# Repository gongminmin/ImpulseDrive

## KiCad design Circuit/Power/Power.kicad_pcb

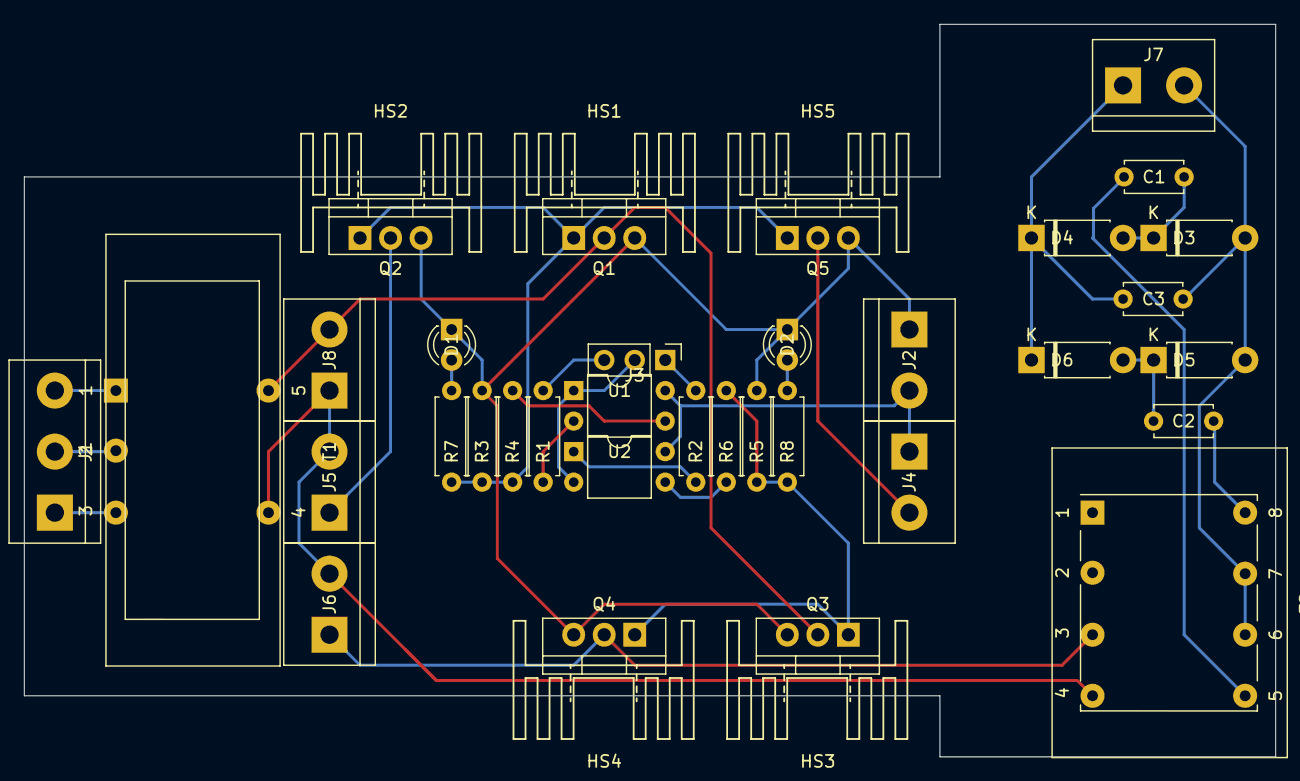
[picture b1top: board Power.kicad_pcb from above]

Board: 2 copper layers, 104.1 x 61.0 mm, 39 parts (0 on the bottom side), 27 nets.

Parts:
C1, C2, C3: 1nF; C_Disc_D4.7mm_W2.5mm_P5.00mm
D1: Discharge; LED_D3.0mm_FlatTop
D2: Charge; LED_D3.0mm_FlatTop
D3, D4, D5, D6: 1N4007; D_DO-41_SOD81_P7.62mm_Horizontal
HS1, HS2, HS3, HS4, HS5: Heatsink; Heatsink_TO220_15x10mm
J1: 12V AC In; TerminalBlock_bornier-3_P5.08mm
J2: DC In; TerminalBlock_bornier-2_P5.08mm
J3: From Control; PinHeader_1x03_P2.54mm_Vertical
J4: To Coil; TerminalBlock_bornier-2_P5.08mm
J5: To Starter; TerminalBlock_bornier-2_P5.08mm
J6: To Capacitor; TerminalBlock_bornier-2_P5.08mm
J7: To Capacitors; TerminalBlock_bornier-2_P5.08mm
J8: AC In; TerminalBlock_bornier-2_P5.08mm
Q1, Q2, Q3, Q4, Q5: RFP30N06LE; TO-220-3_Vertical
R1, R2: 1K; R_Axial_DIN0207_L6.3mm_D2.5mm_P7.62mm_Horizontal
R3, R4, R5, R6: 10K; R_Axial_DIN0207_L6.3mm_D2.5mm_P7.62mm_Horizontal
R7, R8: 3K3; R_Axial_DIN0207_L6.3mm_D2.5mm_P7.62mm_Horizontal
T1: 7+7:14; Transformer_Toroid_5Pin
T2: 6:200; Transformer_Generic_EE25_8Pin
U1, U2: PC817; DIP-4_W7.62mm

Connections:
+12V: J2.2, J4.1, U1.4, U2.4
/AC0In: J1.2, T1.2
/AC+In: J1.3, T1.1
/AC-In: J1.1, T1.3
/CapacitorPower+: C3.1, D4.1, D6.1, J7.1
/CapacitorPower-: C3.2, D3.2, D5.2, J7.2, T2.6, T2.7
/Coil-: J4.2, Q5.2
/ControlGND: J3.3, R1.1
/ControlPower: J3.1, R2.1
/ControlSignal: J3.2, U1.1, U2.2
/StarterPower+: J5.1, Q2.2
/StarterPower-: J5.2, J6.2, J8.1, T1.4, T2.4
GND: D1.1, D2.1, J2.1, Q1.3, Q2.3, Q3.3, Q4.3, Q5.3, R3.1, R5.2
unnamed: C1.1, D3.1, D4.2
unnamed: C1.2, T2.5
unnamed: C2.1, D5.1, D6.2
unnamed: C2.2, T2.8
unnamed: D1.2, R7.1
unnamed: D2.2, R8.2
unnamed: J6.1, Q4.2, T2.3
unnamed: J8.2, Q1.2, Q3.2, T1.5
unnamed: Q1.1, Q2.1, Q5.1, R3.2, R4.2, R7.2
unnamed: Q3.1, Q4.1, R5.1, R6.2, R8.1
unnamed: R1.2, U1.2
unnamed: R2.2, U2.1
unnamed: R4.1, U1.3
unnamed: R6.1, U2.3

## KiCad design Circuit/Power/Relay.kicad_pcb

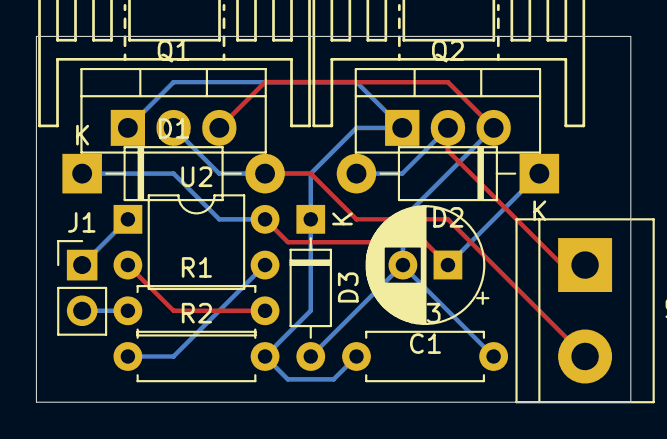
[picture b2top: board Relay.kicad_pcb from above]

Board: 2 copper layers, 33.0 x 20.3 mm, 14 parts (0 on the bottom side), 9 nets.

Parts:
C1: 100uF; CP_Radial_D6.3mm_P2.50mm
D1, D2: 1N4007; D_DO-41_SOD81_P10.16mm_Horizontal
D3: 1N5242B; D_DO-35_SOD27_P7.62mm_Horizontal
HS1, HS2: Heatsink; Heatsink_TO220_15x10mm
J1: Input; PinHeader_1x02_P2.54mm_Vertical
J2: Output; TerminalBlock_bornier-2_P5.08mm
Q1, Q2: RFP30N06LE; TO-220-3_Vertical
R1: 1K; R_Axial_DIN0207_L6.3mm_D2.5mm_P7.62mm_Horizontal
R2, R3: 10K; R_Axial_DIN0207_L6.3mm_D2.5mm_P7.62mm_Horizontal
U2: PC817; DIP-4_W7.62mm

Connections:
/Input+: J1.1, U2.1
/Input-: J1.2, R1.1
/Output1: D1.2, J2.2, Q1.2
/Output2: D2.2, J2.1, Q2.2
unnamed: C1.1, D1.1, D2.1, U2.4
unnamed: C1.2, D3.2, Q1.3, Q2.3, R3.2
unnamed: D3.1, Q1.1, Q2.1, R2.2, R3.1
unnamed: R1.2, U2.2
unnamed: R2.1, U2.3

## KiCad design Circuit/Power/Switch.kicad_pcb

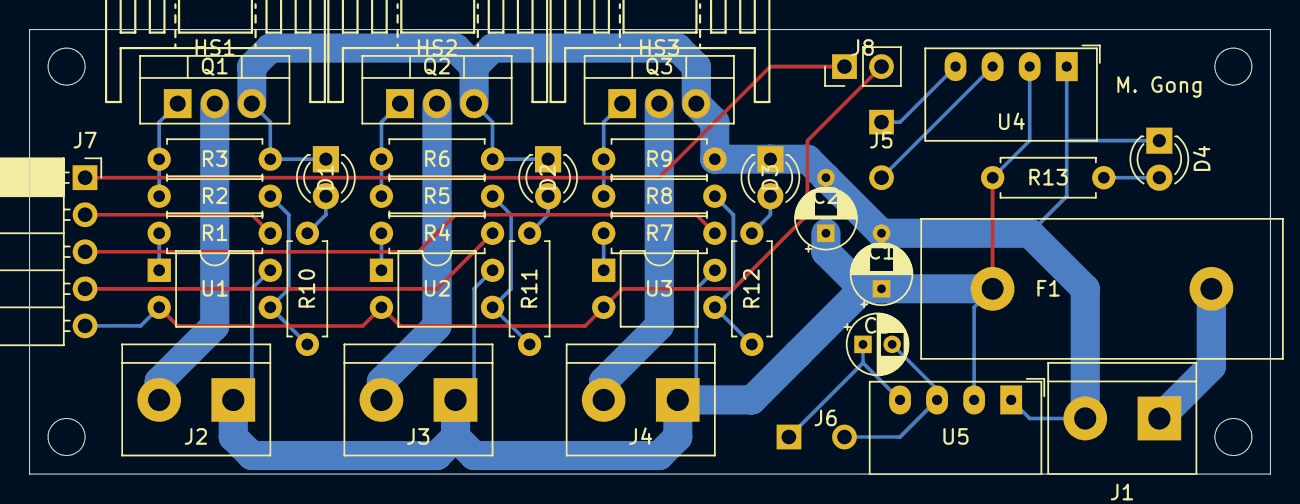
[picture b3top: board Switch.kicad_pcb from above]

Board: 2 copper layers, 85.1 x 30.5 mm, 40 parts (0 on the bottom side), 28 nets.

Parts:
C1, C3: 10uF; CP_Radial_D4.0mm_P2.00mm
C2: 2.2uF; CP_Radial_D4.0mm_P2.00mm
D1, D2, D3, D4: LED; LED_D3.0mm_FlatTop
F1: Fuse; Fuseholder_Cylinder-5x20mm_ASI_PTF-76-10_Horizontal_Open
HS1, HS2, HS3: Heatsink; Heatsink_TO220_15x10mm
J1: Main Power In; TerminalBlock_bornier-2_P5.08mm
J2: To Starter; TerminalBlock_bornier-2_P5.08mm
J3: To Capacitor; TerminalBlock_bornier-2_P5.08mm
J4: To Injector; TerminalBlock_bornier-2_P5.08mm
J5: To Coil; SolderWirePad_1x02_P3.81mm_Drill1mm
J6: To Control Power; SolderWirePad_1x02_P3.81mm_Drill1mm
J7: From Control; PinSocket_1x05_P2.54mm_Horizontal
J8: To Coil Signal; PinHeader_1x02_P2.54mm_Vertical
Q1, Q2, Q3: RFP30N06LE; TO-220-3_Vertical
R1, R4, R7: 680; R_Axial_DIN0207_L6.3mm_D2.5mm_P7.62mm_Horizontal
R2, R5, R8: 4.7K; R_Axial_DIN0207_L6.3mm_D2.5mm_P7.62mm_Horizontal
R3, R6, R9: 10K; R_Axial_DIN0207_L6.3mm_D2.5mm_P7.62mm_Horizontal
R10, R11, R12, R13: 2.2K; R_Axial_DIN0207_L6.3mm_D2.5mm_P7.62mm_Horizontal
U1, U2, U3: PC817; DIP-4_W7.62mm
U4: B1212S; Converter_DCDC_muRata_CRE1xxxxxxSC_THT
U5: B1205S; Converter_DCDC_muRata_CRE1xxxxxxSC_THT

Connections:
/CapacitorPower+: C1.1, C2.1, F1.1, J2.1, J3.1, J4.1, R13.1, U1.4, U2.4, U3.4, U4.2, U5.2
/CapacitorPower-: J3.2, Q2.2
/CapacitorSignal: J7.4, R4.1
/CoilPower+: J5.1, U4.4
/CoilPower-: J5.2, U4.3
/CoilSignal: J7.1, J8.1
/ControlPower+: C3.1, J6.1, U5.4
/ControlPower-: C3.2, J6.2, U5.3
/InjectorPower-: J4.2, Q3.2
/InjectorSignal: J7.3, R7.1
/PowerIn+: F1.2, J1.1
/PowerIn-: C1.2, C2.2, D1.1, D2.1, D3.1, D4.1, J1.2, Q1.3, Q2.3, Q3.3, R3.2, R6.2, R9.2, U4.1, U5.1
/SignalGND: J7.5, J8.2, U1.2, U2.2, U3.2
/StarterPower-: J2.2, Q1.2
/StarterSignal: J7.2, R1.1
unnamed: D1.2, R10.2
unnamed: D2.2, R11.2
unnamed: D3.2, R12.2
unnamed: D4.2, R13.2
unnamed: Q1.1, R2.2, R3.1
unnamed: Q2.1, R5.2, R6.1
unnamed: Q3.1, R8.2, R9.1
unnamed: R1.2, U1.1
unnamed: R4.2, U2.1
unnamed: R7.2, U3.1
unnamed: R2.1, R10.1, U1.3
unnamed: R5.1, R11.1, U2.3
unnamed: R8.1, R12.1, U3.3

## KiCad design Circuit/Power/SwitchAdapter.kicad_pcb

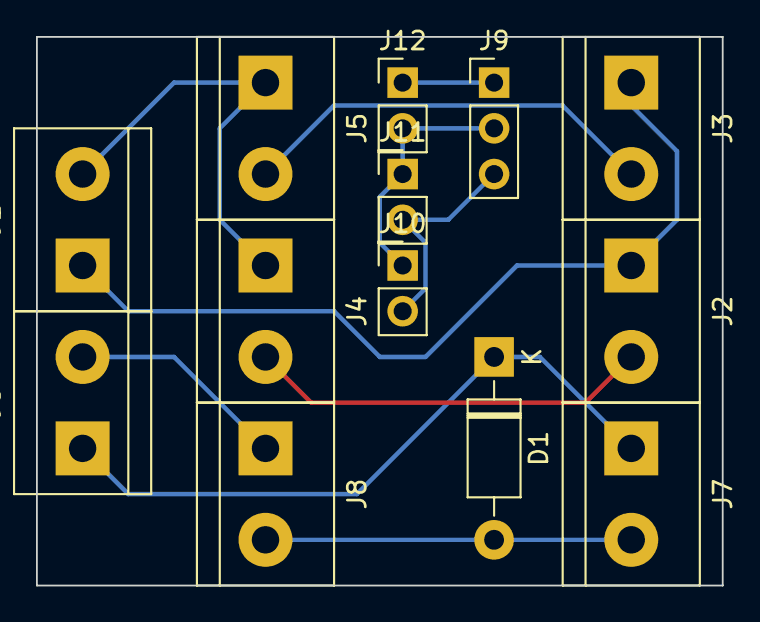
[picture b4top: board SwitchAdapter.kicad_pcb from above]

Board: 2 copper layers, 38.1 x 30.5 mm, 13 parts (0 on the bottom side), 10 nets.

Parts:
D1: 1N4007; D_DO-41_SOD81_P10.16mm_Horizontal
J1: Power AC In; TerminalBlock_bornier-2_P5.08mm
J2: To Starter; TerminalBlock_bornier-2_P5.08mm
J3: To Capacitor; TerminalBlock_bornier-2_P5.08mm
J4: Starter Relay Output; TerminalBlock_bornier-2_P5.08mm
J5: Capacitor Relay Output; TerminalBlock_bornier-2_P5.08mm
J6: DC In; TerminalBlock_bornier-2_P5.08mm
J7: To Coil; TerminalBlock_bornier-2_P5.08mm
J8: Coil Relay Output; TerminalBlock_bornier-2_P5.08mm
J9: From Control; PinHeader_1x03_P2.54mm_Vertical
J10: Coil Signal; PinHeader_1x02_P2.54mm_Vertical
J11: Starter Signal; PinHeader_1x02_P2.54mm_Vertical
J12: Capacitor Signal; PinHeader_1x02_P2.54mm_Vertical

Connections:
/CapacitorPower+: J3.2, J5.2
/CapacitorPower-: J1.1, J2.1, J3.1
/CapacitorRelayIn: J1.2, J4.1, J5.1
/CapacitorSignal+: J9.1, J12.1
/CapacitorSignal-: J9.2, J10.1, J11.1, J12.2
/CoilPower+: D1.1, J6.1, J7.1
/CoilPower-: J6.2, J8.1
/CoilRelayOut: D1.2, J7.2, J8.2
/CoilSignal-: J9.3, J10.2, J11.2
/StarterPower+: J2.2, J4.2

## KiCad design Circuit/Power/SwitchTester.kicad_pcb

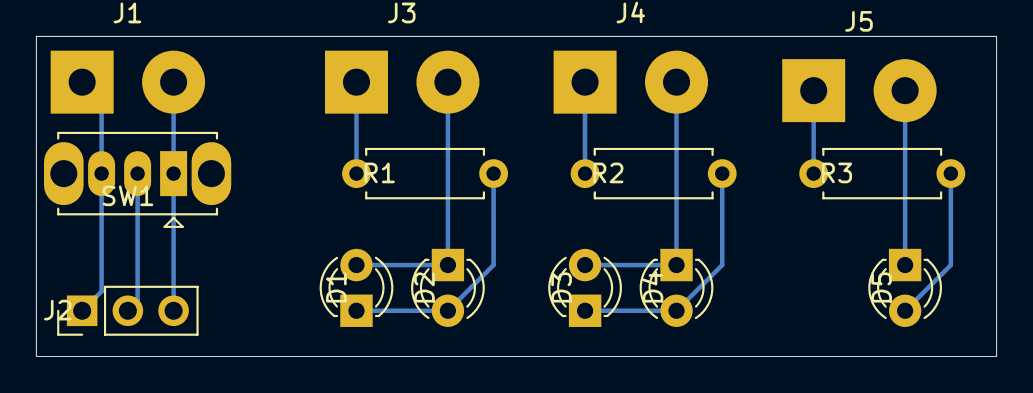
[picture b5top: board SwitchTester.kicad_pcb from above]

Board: 2 copper layers, 53.3 x 17.8 mm, 14 parts (0 on the bottom side), 12 nets.

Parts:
D1, D2, D3, D4, D5: LED; LED_D3.0mm_FlatTop
J1: 12V Power; SolderWirePad_1x02_P5.08mm_Drill1.5mm
J2: As Control; PinHeader_1x03_P2.54mm_Vertical
J3: As Starter; SolderWirePad_1x02_P5.08mm_Drill1.5mm
J4: As Capacitor; SolderWirePad_1x02_P5.08mm_Drill1.5mm
J5: As Coil; SolderWirePad_1x02_P5.08mm_Drill1.5mm
R1, R2, R3: 2K2; R_Axial_DIN0207_L6.3mm_D2.5mm_P7.62mm_Horizontal
SW1: SW_SPDT; SW_Slide_1P2T_CK_OS102011MS2Q

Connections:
GND: J1.2, J2.3, SW1.1
unnamed: D1.1, D2.2, R1.2
unnamed: D1.2, D2.1, J3.2
unnamed: D3.1, D4.2, R2.2
unnamed: D3.2, D4.1, J4.2
unnamed: D5.1, J5.2
unnamed: D5.2, R3.2
unnamed: J1.1, J2.1, SW1.3
unnamed: J2.2, SW1.2
unnamed: J3.1, R1.1
unnamed: J4.1, R2.1
unnamed: J5.1, R3.1

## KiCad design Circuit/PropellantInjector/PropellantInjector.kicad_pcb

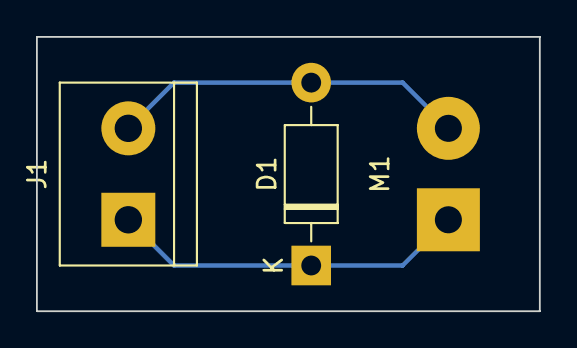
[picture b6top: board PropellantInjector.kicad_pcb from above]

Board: 2 copper layers, 27.9 x 15.2 mm, 3 parts (0 on the bottom side), 2 nets.

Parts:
D1: 1N4007; D_DO-41_SOD81_P10.16mm_Horizontal
J1: Injector Power; TerminalBlock_bornier-2_P5.08mm
M1: Motor_DC; SolderWirePad_1x02_P5.08mm_Drill1.5mm

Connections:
/InjectorPower+: D1.1, J1.1, M1.1
/InjectorPower-: D1.2, J1.2, M1.2
